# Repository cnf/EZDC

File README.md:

# EZCPAP

EZCPAP is a BLDC driver for [CPAP blower motors](https://www.ifixit.com/Guide/ResMed+AirSense+10+Pump+Motor+Replacement/137050) that fits in a BTT EZDriver socket, such as on an [SKR EZ](https://bttwiki.com/SKR%203%20EZ.html).

It effectively acts like a motor driver on a 3d printer. which you can then use to drive a CPAP motor for part cooling.

!! Still in the conceptual/development phase !!

[View in kicanvas](https://kicanvas.org/?github=https%3A%2F%2Fgithub.com%2Fcnf%2FEZCPAP)

## Concept render

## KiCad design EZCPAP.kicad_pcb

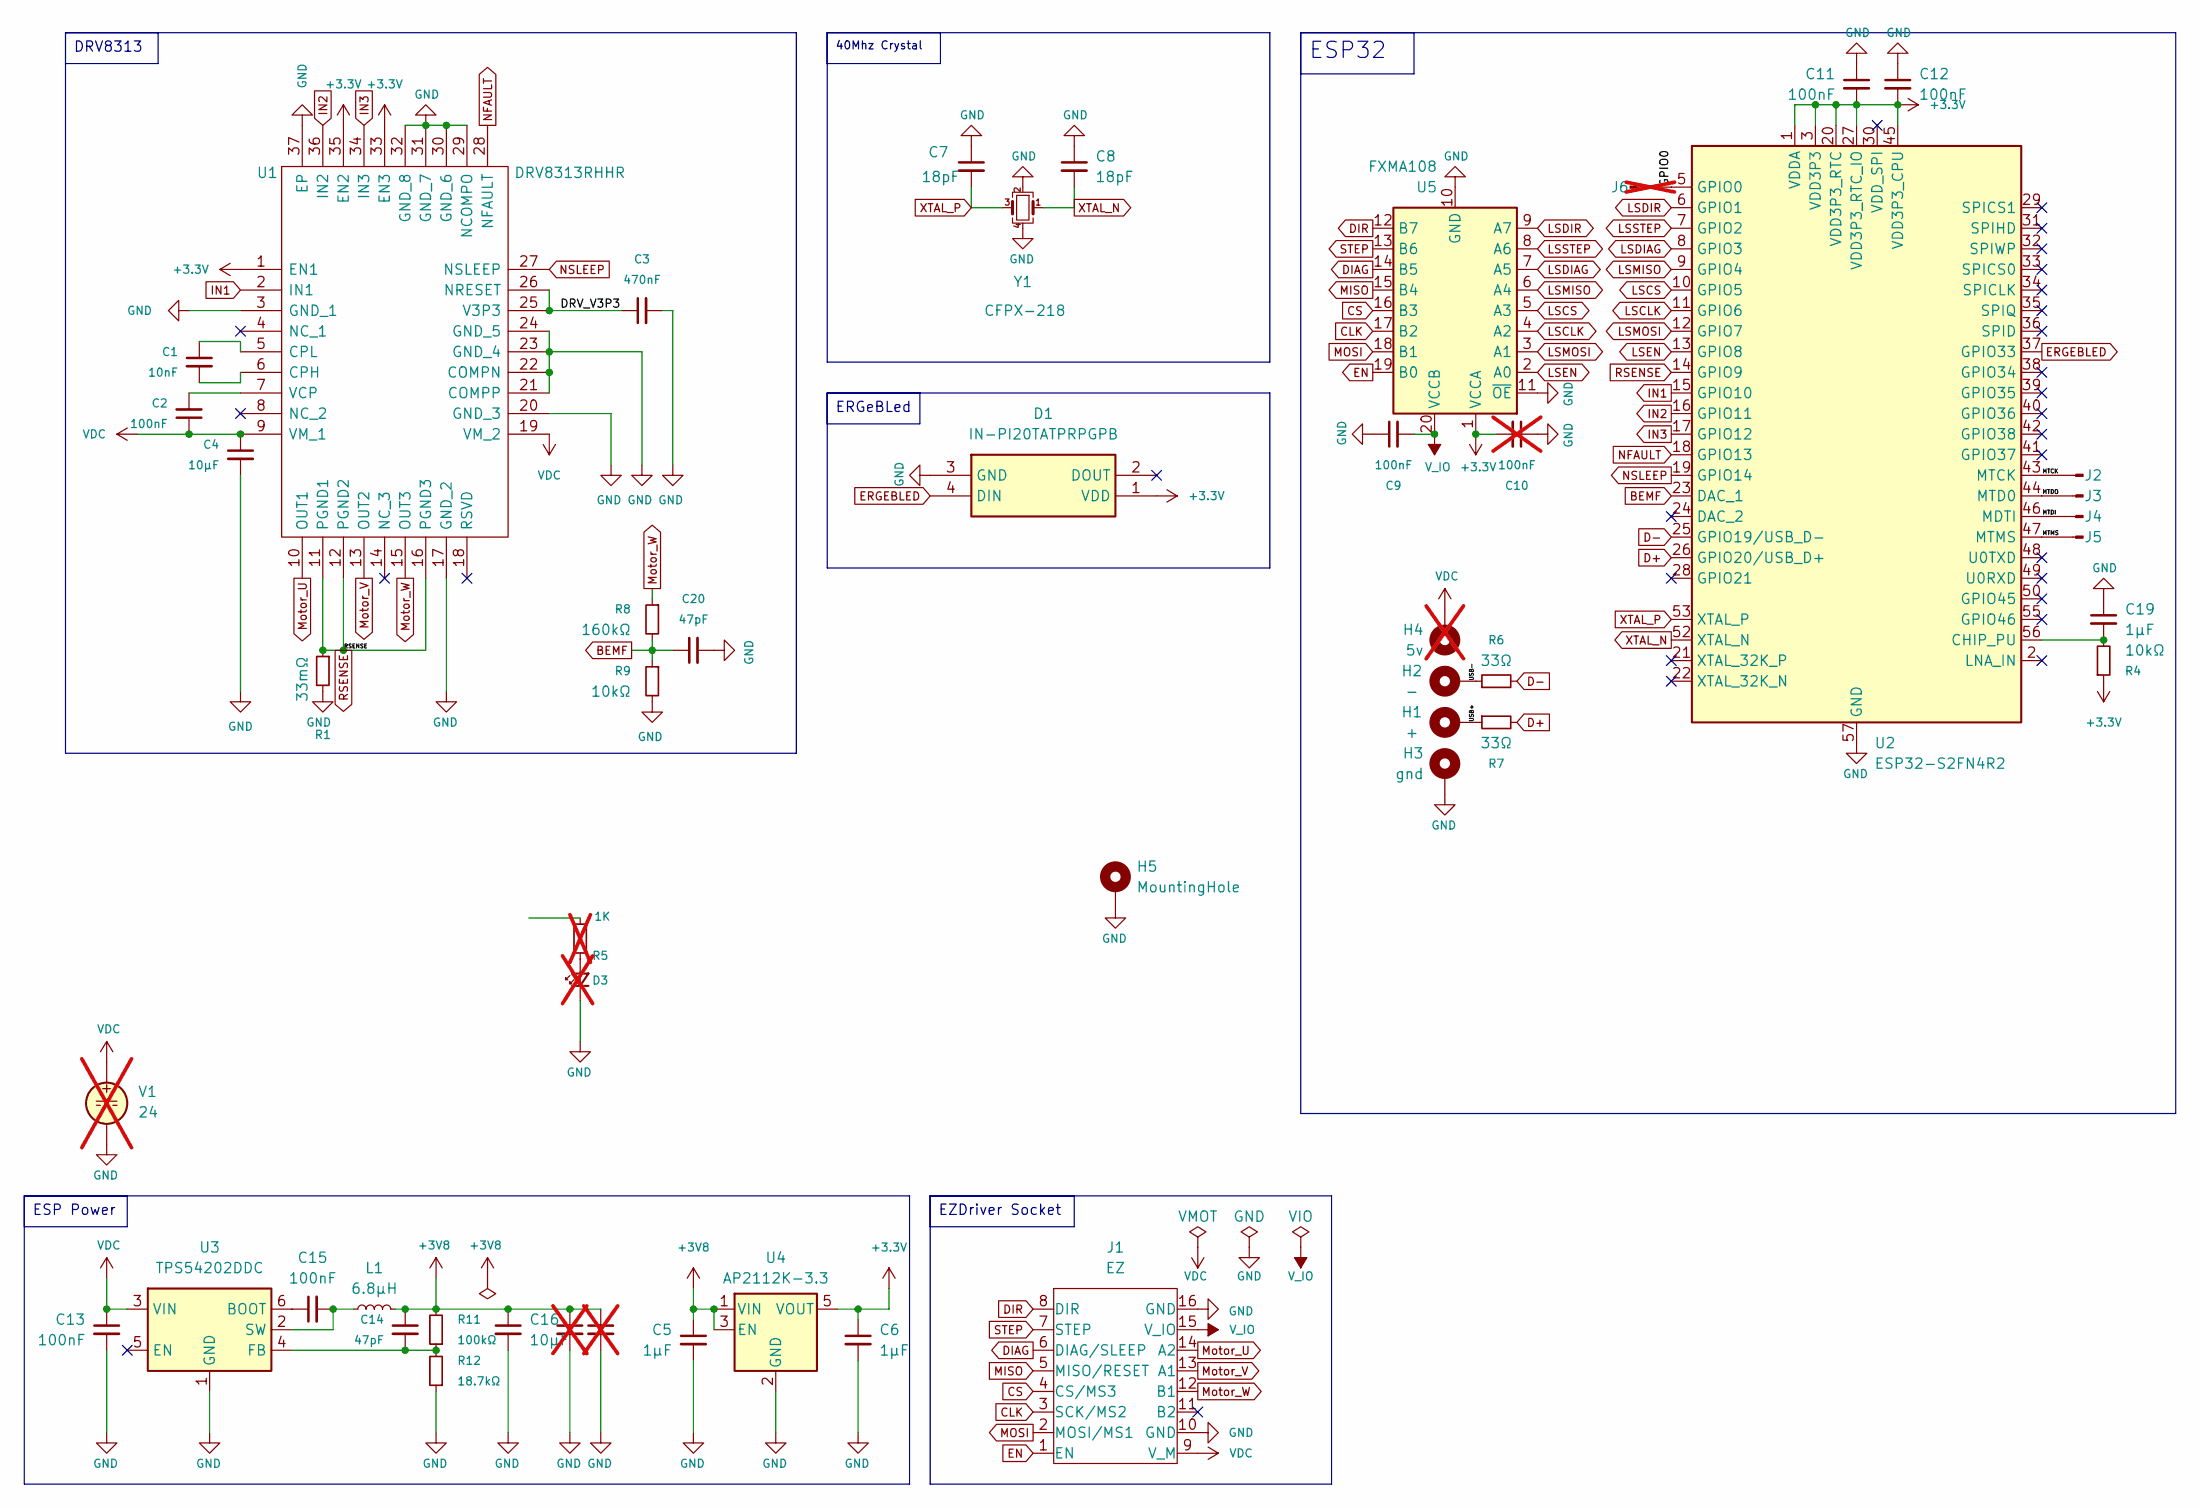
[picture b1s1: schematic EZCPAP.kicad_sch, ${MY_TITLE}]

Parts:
C1: 10nF; C_0402_1005Metric_Pad0.74x0.62mm_HandSolder
C2, C9, C11, C12, C13, C15: 100nF; C_0402_1005Metric_Pad0.74x0.62mm_HandSolder
C3: 470nF; C_0402_1005Metric_Pad0.74x0.62mm_HandSolder
C4, C16: 10µF; C_0805_2012Metric_Pad1.18x1.45mm_HandSolder
C5, C6, C19: 1µF; C_0402_1005Metric_Pad0.74x0.62mm_HandSolder
C7, C8: 18pF; C_0402_1005Metric_Pad0.74x0.62mm_HandSolder
C10: 100nF; C_0402_1005Metric_Pad0.74x0.62mm_HandSolder; LCSC Part C307331; not fitted
C14, C20: 47pF; C_0402_1005Metric_Pad0.74x0.62mm_HandSolder
C17, C18: NaN; C_0402_1005Metric_Pad0.74x0.62mm_HandSolder; LCSC Part C23733; not fitted
D1: IN-PI20TATPRPGPB; LED_2020; Manufacturer_Part_Number IN-PI20TATPRPGPB; Mouser Part Number 743-IN-PI20TATPRPGPB
D3: Green; LED_0402_1005Metric; not fitted
H1: +; TestPoint_Pad_1.0x1.0mm
H2: -; TestPoint_Pad_1.0x1.0mm
H3: gnd; TestPoint_Pad_1.0x1.0mm
H4: 5v; TestPoint_Pad_1.0x1.0mm; not fitted
H5: MountingHole; Hole
J1: EZ; EZDriver
J2, J3, J4, J5: Conn_01x01_Pin; Pin Exposed Pad
J6: Conn_01x01_Pin; Pin Exposed Pad; not fitted
L1: 6.8µH; L_Wurth_WE-MAPI-3020; Part Number 74438336068HT
R1: 33mΩ; R_0805_2012Metric
R4, R9: 10kΩ; R_0402_1005Metric_Pad0.72x0.64mm_HandSolder
R5: 1K; R_0402_1005Metric_Pad0.72x0.64mm_HandSolder; not fitted
R6, R7: 33Ω; R_0402_1005Metric_Pad0.72x0.64mm_HandSolder
R8: 160kΩ; R_0402_1005Metric_Pad0.72x0.64mm_HandSolder
R11: 100kΩ; R_0402_1005Metric_Pad0.72x0.64mm_HandSolder
R12: 18.7kΩ; R_0402_1005Metric_Pad0.72x0.64mm_HandSolder
U1: DRV8313RHHR; DRV8313RHH; Manufacturer PN DRV8313RHHR; LCSC Part C165154
U2: ESP32-S2FN4R2; QFN-56-1EP_7x7mm_P0.4mm_EP4x4mm_ThermalVias; LCSC Part C2844252
U3: TPS54202DDC; SOT-23-6; LCSC Part C191884
U4: AP2112K-3.3; SOT-23-5; LCSC Part C51118
U5: FXMA108; WQFN-20-1EP_2.5x4.5mm_P0.5mm_EP1x2.9mm; LCSC Part C891320
V1: 24; not fitted
Y1: CFPX-218; Crystal_SMD_2520-4Pin_2.5x2.0mm; Manufacturer PN 830108208709

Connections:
+3.3V: C6.1, C10.2, C11.2, C12.2, D1.1 (VDD), R4.1, U1.1 (EN1), U1.33 (EN3), U1.35 (EN2), U2.1 (VDDA), U2.3 (VDD3P3), U2.4 (VDD3P3), U2.20 (VDD3P3_RTC), U2.27 (VDD3P3_RTC_IO), U2.45 (VDD3P3_CPU), U2.51 (VDDA), U2.54 (VDDA), U4.5 (VOUT), U5.1 (VCCA)
+3V8: C5.1, C14.1, C16.1, C17.1, C18.1, L1.2, R11.2, U4.1 (VIN), U4.3 (EN)
/DRV_V3P3: C3.1, U1.25 (V3P3), U1.26 (NRESET)
/GPIO0: J6.1, U2.5 (GPIO0)
/MTCK: J2.1, U2.43 (MTCK)
/MTDI: J4.1, U2.46 (MDTI)
/MTDO: J3.1, U2.44 (MTD0)
/MTMS: J5.1, U2.47 (MTMS)
/USB+: H1.1, R7.1
/USB-: H2.1, R6.1
BEMF: C20.1, R8.2, R9.1, U2.23 (DAC_1)
CLK: J1.3 (SCK/MS2), U5.17 (B2)
CS: J1.4 (CS/MS3), U5.16 (B3)
D+: R7.2, U2.26 (GPIO20/USB_D+)
D-: R6.2, U2.25 (GPIO19/USB_D-)
DIAG: J1.6 (DIAG/SLEEP), U5.14 (B5)
DIR: J1.8 (DIR), U5.12 (B7)
EN: J1.1 (EN), U5.19 (B0)
ERGEBLED: D1.4 (DIN), U2.37 (GPIO33)
GND: C3.2, C4.2, C5.2, C6.2, C7.1, C8.1, C9.1, C10.1, C11.1, C12.1, C13.2, C16.2, C17.2, C18.2, C19.1, C20.2, D1.3 (GND), D3.1 (K), H3.1, H5.1, J1.10 (GND), J1.16 (GND), R1.2, R9.2, R12.1, U1.3 (GND_1), U1.17 (GND_2), U1.20 (GND_3), U1.21 (COMPP), U1.22 (COMPN), U1.23 (GND_4), U1.24 (GND_5), U1.29 (NCOMPO), U1.30 (GND_6), U1.31 (GND_7), U1.32 (GND_8), U1.37 (EP), U2.57 (GND), U3.1 (GND), U4.2 (GND), U5.10 (GND), U5.11 (~OE), V1.2, Y1.2, Y1.4
IN1: U1.2 (IN1), U2.15 (GPIO10)
IN2: U1.36 (IN2), U2.16 (GPIO11)
IN3: U1.34 (IN3), U2.17 (GPIO12)
LSCLK: U2.11 (GPIO6), U5.4 (A2)
LSCS: U2.10 (GPIO5), U5.5 (A3)
LSDIAG: U2.8 (GPIO3), U5.7 (A5)
LSDIR: U2.6 (GPIO1), U5.9 (A7)
LSEN: U2.13 (GPIO8), U5.2 (A0)
LSMISO: U2.9 (GPIO4), U5.6 (A4)
LSMOSI: U2.12 (GPIO7), U5.3 (A1)
LSSTEP: U2.7 (GPIO2), U5.8 (A6)
MISO: J1.5 (MISO/RESET), U5.15 (B4)
MOSI: J1.2 (MOSI/MS1), U5.18 (B1)
Motor_U: J1.14 (A2), U1.10 (OUT1)
Motor_V: J1.13 (A1), U1.13 (OUT2)
Motor_W: J1.12 (B1), R8.1, U1.15 (OUT3)
NFAULT: U1.28 (NFAULT), U2.18 (GPIO13)
NSLEEP: U1.27 (NSLEEP), U2.19 (GPIO14)
unnamed: D3.2 (A), R5.1
unnamed: C1.2, U1.6 (CPH)
unnamed: C1.1, U1.5 (CPL)
unnamed: C2.2, U1.7 (VCP)
unnamed: C19.2, R4.2, U2.56 (CHIP_PU)
unnamed: C15.1, U3.6 (BOOT)
unnamed: C14.2, R11.1, R12.2, U3.4 (FB)
unnamed: C15.2, L1.1, U3.2 (SW)
RSENSE: R1.1, U1.11 (PGND1), U1.12 (PGND2), U1.16 (PGND3), U2.14 (GPIO9)
STEP: J1.7 (STEP), U5.13 (B6)
VDC: C2.1, C4.1, C13.1, H4.1, J1.9 (V_M), U1.9 (VM_1), U1.19 (VM_2), U3.3 (VIN), V1.1
V_IO: C9.2, J1.15 (V_IO), U5.20 (VCCB)
XTAL_N: C8.2, U2.52 (XTAL_N), Y1.1
XTAL_P: C7.2, U2.53 (XTAL_P), Y1.3

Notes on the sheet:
40Mhz Crystal
DRV8313
ERGeBLed
ESP32
EZDriver Socket
ESP Power

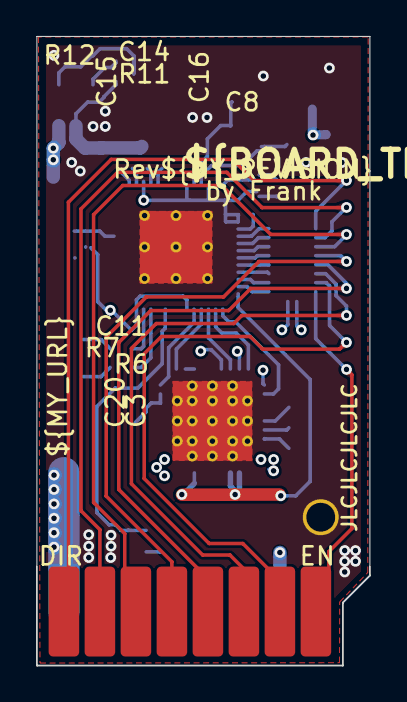
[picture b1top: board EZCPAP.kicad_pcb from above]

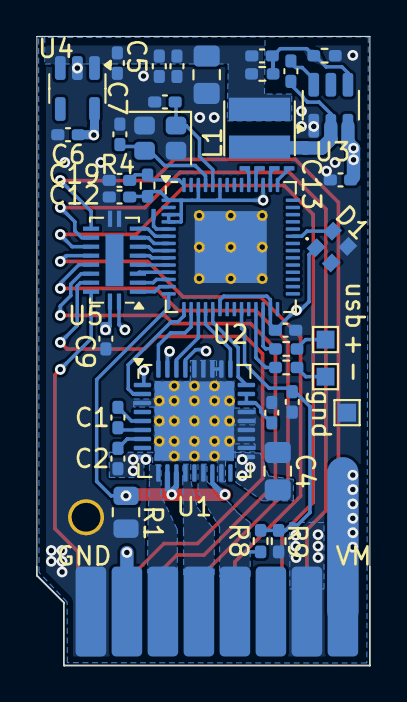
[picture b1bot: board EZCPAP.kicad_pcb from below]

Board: 4 copper layers, 18.5 x 35.0 mm, 45 parts (44 on the bottom side), 51 nets.

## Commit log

2025-08-09 initial
2025-08-10 right level shifter ref networks, and small changes
2025-08-10 Adding extra footprints/symbols to project
2025-08-10 moar cleanup n stuff
2025-08-10 moved via intercecting with a trace
2025-08-12 added hole, etc
2025-08-12 more cleanup, hard enable, but link nsleep
2025-08-12 added readme
2025-08-12 added kicanvas link
2025-08-18 maybe final
2025-08-18 full vias, and small edits
2025-08-21 maybe, maybe final?
2025-08-22 final, finaller, est?
2025-08-24 final, finaller, ist?
2025-09-22 Update PCB Rendering
2025-10-08 Rev B, initial
2025-10-09 Rev B, RC2
2025-10-09 Rev B, RC3
2025-10-09 Rev B
2025-10-09 Aisler changes
2025-10-23 anularize all the vias
2025-10-24 adding test points
2025-10-24 Fix 3d models
2025-10-24 cleanup
2025-10-24 cosmetics n stuff
